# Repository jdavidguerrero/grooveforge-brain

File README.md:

# GrooveForge Brain

> *"Una pieza de hardware. Cinco niveles de superpoderes. Tú decidís hasta dónde llegar."*

Boutique hybrid AI synthesizer — Teensy 4.1 + ESP32-S3 + discrete 2N3904 ladder filter.

**Retail: $599 USD · BOM: ~$110 · Margin: 82%**

---

## The 5 Levels (North Star)

```
NIVEL 0 — STANDALONE   → 6 synth engines + analog ladder filter + 12 signature FX
NIVEL 1 — + MIDI KB    → Scale Lock, Chord Recognition, Beat Follower (TinyML)
NIVEL 2 — + SLAVES     → E-Drum, Marimba, Air-Bamboo ecosystem (v1.x)
NIVEL 3 — + WIFI       → Patch search NL, progression suggester (cloud AI)
NIVEL 4 — + DAW        → GroovePilot VST3 mix-aware co-pilot
```

---

## Architecture

| Component | Chip | Role |
|---|---|---|
| Audio Brain | Teensy 4.1 (Cortex-M7 @ 600MHz) | Synth engines, FX, TinyML, MIDI |
| Network + UI | ESP32-S3 + GC9A01 1.28" display | WiFi, BLE, cloud sync, OTA |
| Audio Codec | SGTL5000 | 24-bit/48kHz ADC + DAC |
| Analog Filter | Discrete 2N3904 ladder (Moog 1970) | THE analog character |

Audio path: `Teensy → I2S → SGTL5000 → 2N3904 ladder → SGTL5000 ADC → USB Audio`

---

## Monorepo Structure

```
apps/
├── firmware-teensy/   C++ — Teensy 4.1 (PlatformIO)
├── firmware-esp32/    C++ — ESP32-S3 (PlatformIO)
├── bridge-protocol/   C headers — shared protocol
├── hardware/          KiCad PCB schematics
├── design/            Industrial design (3D + Figma)
├── training/          Python — TinyML model training
└── docs/              OpenSpec documentation (SSoT)
tools/
├── matching-jig/      Arduino — transistor Vbe matching jig
└── filter-cal/        Calibration scripts
```

---

## Quick Start

```bash
# Build Teensy firmware
cd apps/firmware-teensy && pio run -e teensy41 -t upload

# Build ESP32 firmware
cd apps/firmware-esp32 && pio run -e esp32s3 -t upload

# Run tests (native, no hardware needed)
pnpm test:native

# ML training
cd apps/training && uv sync && uv run pytest
```

---

## Documentation

All specs live in [`apps/docs/`](apps/docs/README.md):

| Doc | Content |
|---|---|
| [00-master-strategy.md](apps/docs/00-master-strategy.md) | Vision, pricing, North Star |
| [01-architecture.md](apps/docs/01-architecture.md) | Hardware + software spec |
| [02-bridge-protocol.md](apps/docs/02-bridge-protocol.md) | Teensy ↔ ESP32 ↔ VST3 protocol |
| [03-filter-design.md](apps/docs/03-filter-design.md) | Discrete 2N3904 ladder filter |
| [04-ai-architecture.md](apps/docs/04-ai-architecture.md) | 3-layer AI spec |
| [05-fx-architecture.md](apps/docs/05-fx-architecture.md) | 12 signature effects |
| [06-implementation-roadmap.md](apps/docs/06-implementation-roadmap.md) | Phase & sprint plan |

---

## Status

**Phase 0 — Foundation** · May 2026 · 🟡 In Progress

| Milestone | Status |
|---|---|
| Monorepo + CLAUDE.md + agents + skills | 🟢 Done |
| Sprint 1.1 — Hello Tone (440Hz via I2S) | 🔴 Pending |
| Sprint 1.2 — Multi-OSC + ADSR | 🔴 Pending |
| Sprint 1.3 — Transistor matching jig | 🔴 Pending |
| Sprint 1.4 — Filter protoboard | 🔴 Pending |

---

*GrooveForge Brain · Juan Guerrero (GPROG) · Bogotá, Colombia · 2026*

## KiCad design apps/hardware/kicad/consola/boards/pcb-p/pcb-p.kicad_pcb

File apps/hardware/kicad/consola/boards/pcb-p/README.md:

# PCB-P — pads de fuerza Console

Placa pasiva de 223 × 31 × 1,6 mm, ensamblada a mano. Seis discos FSR402 sobre la placa;
colas por ranuras NPTH a seis sockets HCTL C2897365 inferiores. Se conservan seis JST-PH
J1–J6 de 2 vías y los doce nets independientes del mazo aprobado.

Especificación y cálculo: `docs/THEORY-layout.md`. Resultado y límites: `../../tools/layout/REPORT-p.md`.
Recrear layout con Python de KiCad: `../../tools/layout/layout_p.py`.
La terminación inferior reemplaza la soldadura directa D43.

`placement.csv`: coordenadas de panel, seis datums de disco F. `docs/layout-targets.json`: datums pin 1 de FSR/J B.
Conversión: x_panel=x_KiCad+44; y_panel=371−y_KiCad.
Gerbers y taladros en `fab/`; montaje 1:1 y comprobaciones en `docs/`.

Los identificadores FSR1–FSR6 del esquema se conservan para los landings de sus sockets inferiores.
La huella local reemplaza la geometría D43; su nombre histórico no indica soldadura directa.
La compra de sockets está en `assembly-sockets.csv`, validada con el mismo catálogo y comprobador BOM.

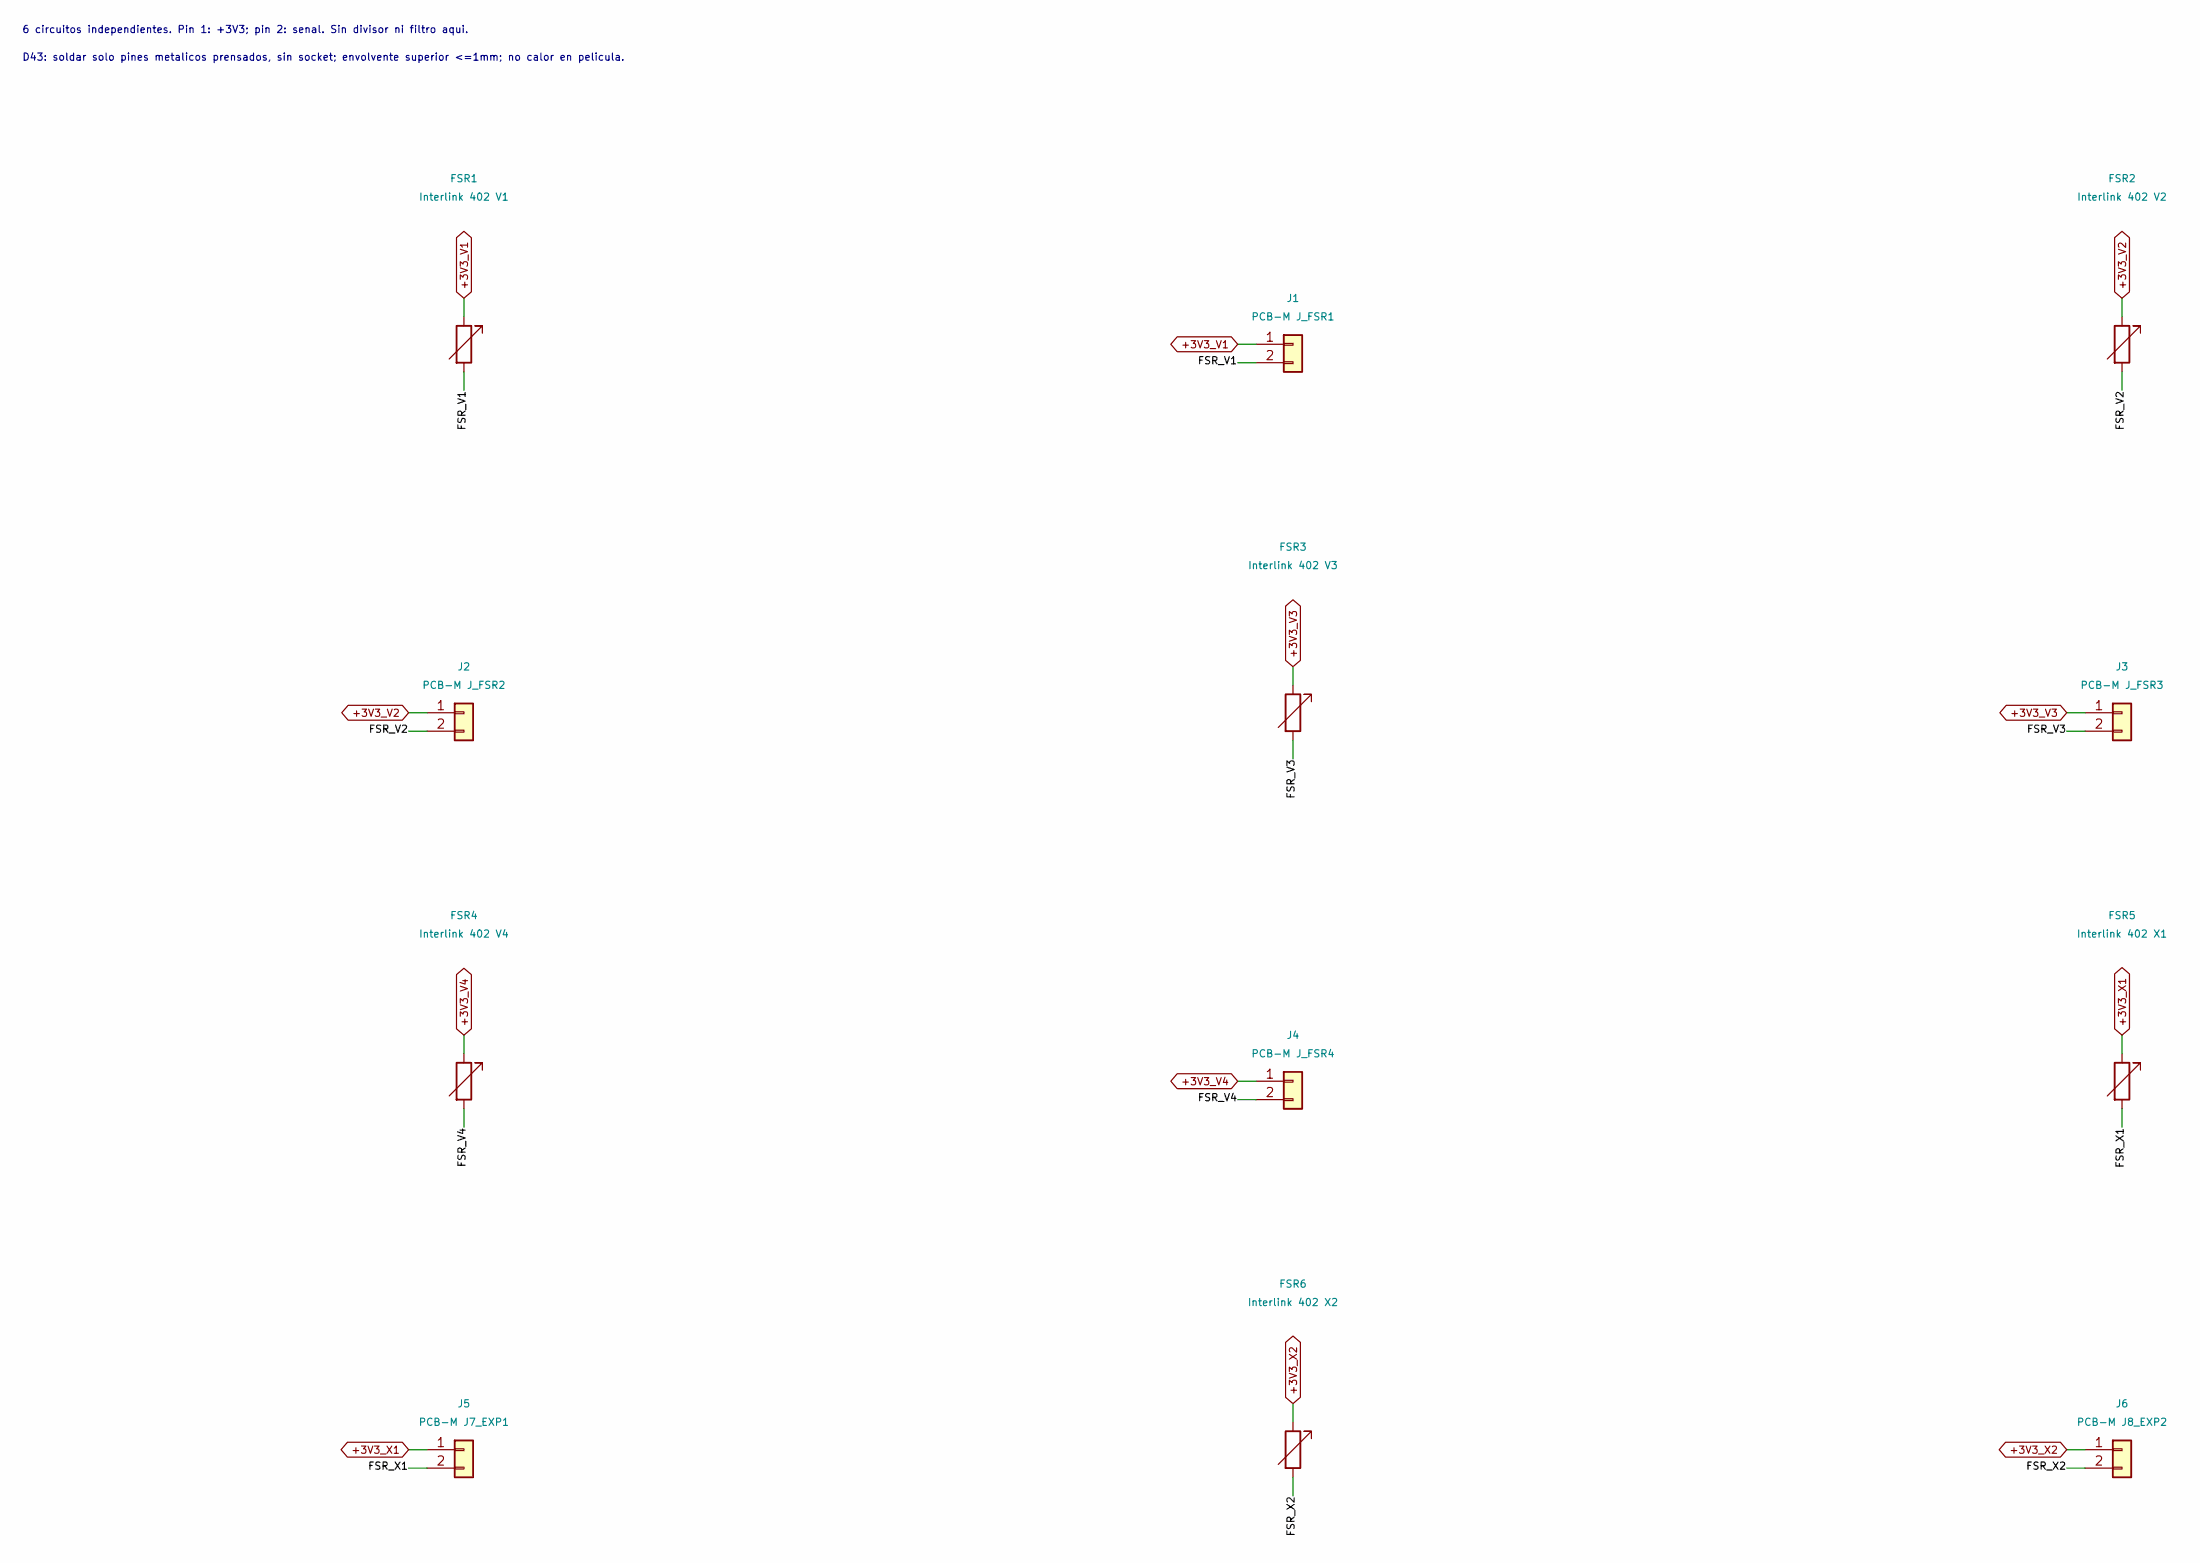
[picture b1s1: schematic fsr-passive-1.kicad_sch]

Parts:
FSR1: Interlink 402 V1; FSR402_DirectSolder_1x02_P2.54mm
FSR2: Interlink 402 V2; FSR402_DirectSolder_1x02_P2.54mm
FSR3: Interlink 402 V3; FSR402_DirectSolder_1x02_P2.54mm
FSR4: Interlink 402 V4; FSR402_DirectSolder_1x02_P2.54mm
FSR5: Interlink 402 X1; FSR402_DirectSolder_1x02_P2.54mm
FSR6: Interlink 402 X2; FSR402_DirectSolder_1x02_P2.54mm
J1: PCB-M J_FSR1; JST_PH_S2B-PH-K_1x02_P2.00mm_Horizontal; MPN S2B-PH-K-S(LF)(SN); LCSC C173752
J2: PCB-M J_FSR2; JST_PH_S2B-PH-K_1x02_P2.00mm_Horizontal; MPN S2B-PH-K-S(LF)(SN); LCSC C173752
J3: PCB-M J_FSR3; JST_PH_S2B-PH-K_1x02_P2.00mm_Horizontal; MPN S2B-PH-K-S(LF)(SN); LCSC C173752
J4: PCB-M J_FSR4; JST_PH_S2B-PH-K_1x02_P2.00mm_Horizontal; MPN S2B-PH-K-S(LF)(SN); LCSC C173752
J5: PCB-M J7_EXP1; JST_PH_S2B-PH-K_1x02_P2.00mm_Horizontal; MPN S2B-PH-K-S(LF)(SN); LCSC C173752
J6: PCB-M J8_EXP2; JST_PH_S2B-PH-K_1x02_P2.00mm_Horizontal; MPN S2B-PH-K-S(LF)(SN); LCSC C173752

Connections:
+3V3_V1: FSR1.1, J1.1
+3V3_V2: FSR2.1, J2.1
+3V3_V3: FSR3.1, J3.1
+3V3_V4: FSR4.1, J4.1
+3V3_X1: FSR5.1, J5.1
+3V3_X2: FSR6.1, J6.1
/fsr-passive-1/FSR_V1: FSR1.2, J1.2
/fsr-passive-1/FSR_V2: FSR2.2, J2.2
/fsr-passive-1/FSR_V3: FSR3.2, J3.2
/fsr-passive-1/FSR_V4: FSR4.2, J4.2
/fsr-passive-1/FSR_X1: FSR5.2, J5.2
/fsr-passive-1/FSR_X2: FSR6.2, J6.2

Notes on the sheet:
6 circuitos independientes. Pin 1: +3V3; pin 2: senal. Sin divisor ni filtro aqui.
D43: soldar solo pines metalicos prensados, sin socket; envolvente superior <=1mm; no calor en pelicula.

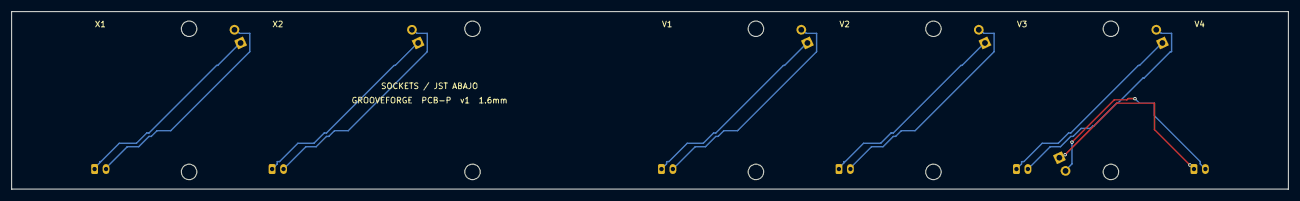
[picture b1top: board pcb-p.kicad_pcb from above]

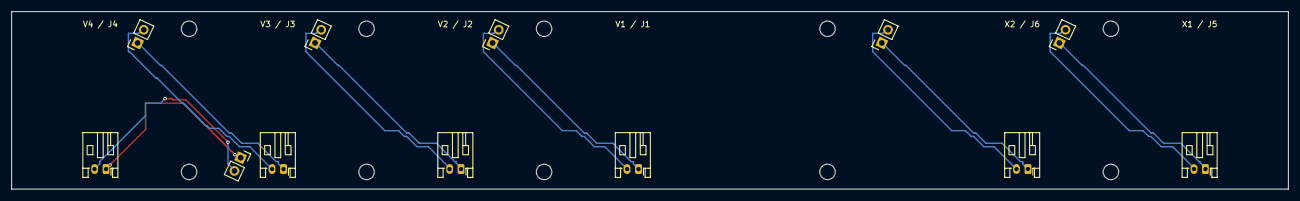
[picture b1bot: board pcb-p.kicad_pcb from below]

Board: 2 copper layers, 223.0 x 31.0 mm, 28 parts (12 on the bottom side), 12 nets.

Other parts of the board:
H1, H2, H3, H4, H5, H6, H7, H8, H9, H10: M2.5 NPTH; MountingHole_2.7mm_M2.5
SLOT1, SLOT2, SLOT3, SLOT4, SLOT5, SLOT6: COLA 3x8.8 NPTH

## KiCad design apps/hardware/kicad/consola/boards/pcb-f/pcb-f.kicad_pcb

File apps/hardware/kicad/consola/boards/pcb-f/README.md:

# PCB-F — GrooveForge Console

Layout de dos capas **81 × 83 mm**, cuatro RS6011 B50K a paso **20 mm**.
El esquema y los CSV originales se conservan. Ver [teoría](docs/THEORY-layout.md)
y [reporte completo](../../tools/layout/REPORT-f.md).

Desde la raíz del clon:

```sh
/Applications/KiCad/KiCad.app/Contents/Frameworks/Python.framework/Versions/Current/bin/python3 apps/hardware/kicad/consola/tools/layout/layout_f.py
```

El script exporta el esquema a XML, compara las seis redes con el XML verificado,
importa sus diez componentes, coloca cuatro M3, enruta, rellena GND, ejecuta DRC y
exporta `fab/` y `docs/`. `--verify-only` verifica la placa guardada;
`--finish-only` rellena, verifica y exporta una placa existente. No escribe esquemas.

Coordenadas: **x_panel = x_KiCad + 44; y_panel = 371 − y_KiCad** (mm).
Faders: F.Cu / 90°; centros según `placement.csv`. J1: **B.Cu / 90°**, origen
panel **(257,5; 160,2)**, boca hacia **−x**; su extremo trasero llega a y=165,1.
La posición deja libres el M3 posterior izquierdo y RV1. Cara superior del FR4:
TOP−9,5; con espesor 1,6, J1 se monta bajo TOP−11,1.

J1 es **1:1** hacia PCB-A J3: **1 +3V3, 2 FADER1, 3 FADER2, 4 FADER3,
5 FADER4, 6 GND**. Los MP del JST se conservan sin red, según el esquema.
Los doce MP de los faders llevan GND sólido. La copia local `groovepush.pretty`
conserva la geometría upstream y añade únicamente `zone_connect 2` a esos pads;
no cambia la biblioteca compartida ni el identificador del esquema.

`fab/`: Gerbers, taladros **PTH y NPTH separados**, job y reporte de taladros.
`docs/`: DRC JSON, verificación geométrica/eléctrica JSON, XML recién exportado,
SVG por capa, plantilla [1:1](docs/pcb-f-assembly-1to1.svg) y DXF Edge.Cuts.
Los agujeros internos se fabrican desde NPTH; el DXF de Edge.Cuts contiene solo
el perímetro exterior, sin convertir taladros en fresados duplicados.

**Antes de pedir:** imprimir el SVG de montaje al 100 %, sin ajustar a página;
medir el paso de 20 mm y el contorno, superponer un RS6011 real y verificar pads,
NPTH, carcasa, carrera, altura, cabezas M3 Ø5,5 y acceso al cable JST por debajo.
No usar arandelas Ø6,4 en las esquinas sin revisar el montaje. El contorno fijo deja
solo 0,25 mm entre cabeza nominal Ø5,5 y borde. Validar continuidad carcasa→GND
y el bond del panel: los cuatro agujeros M3 son NPTH y no realizan ese bond.

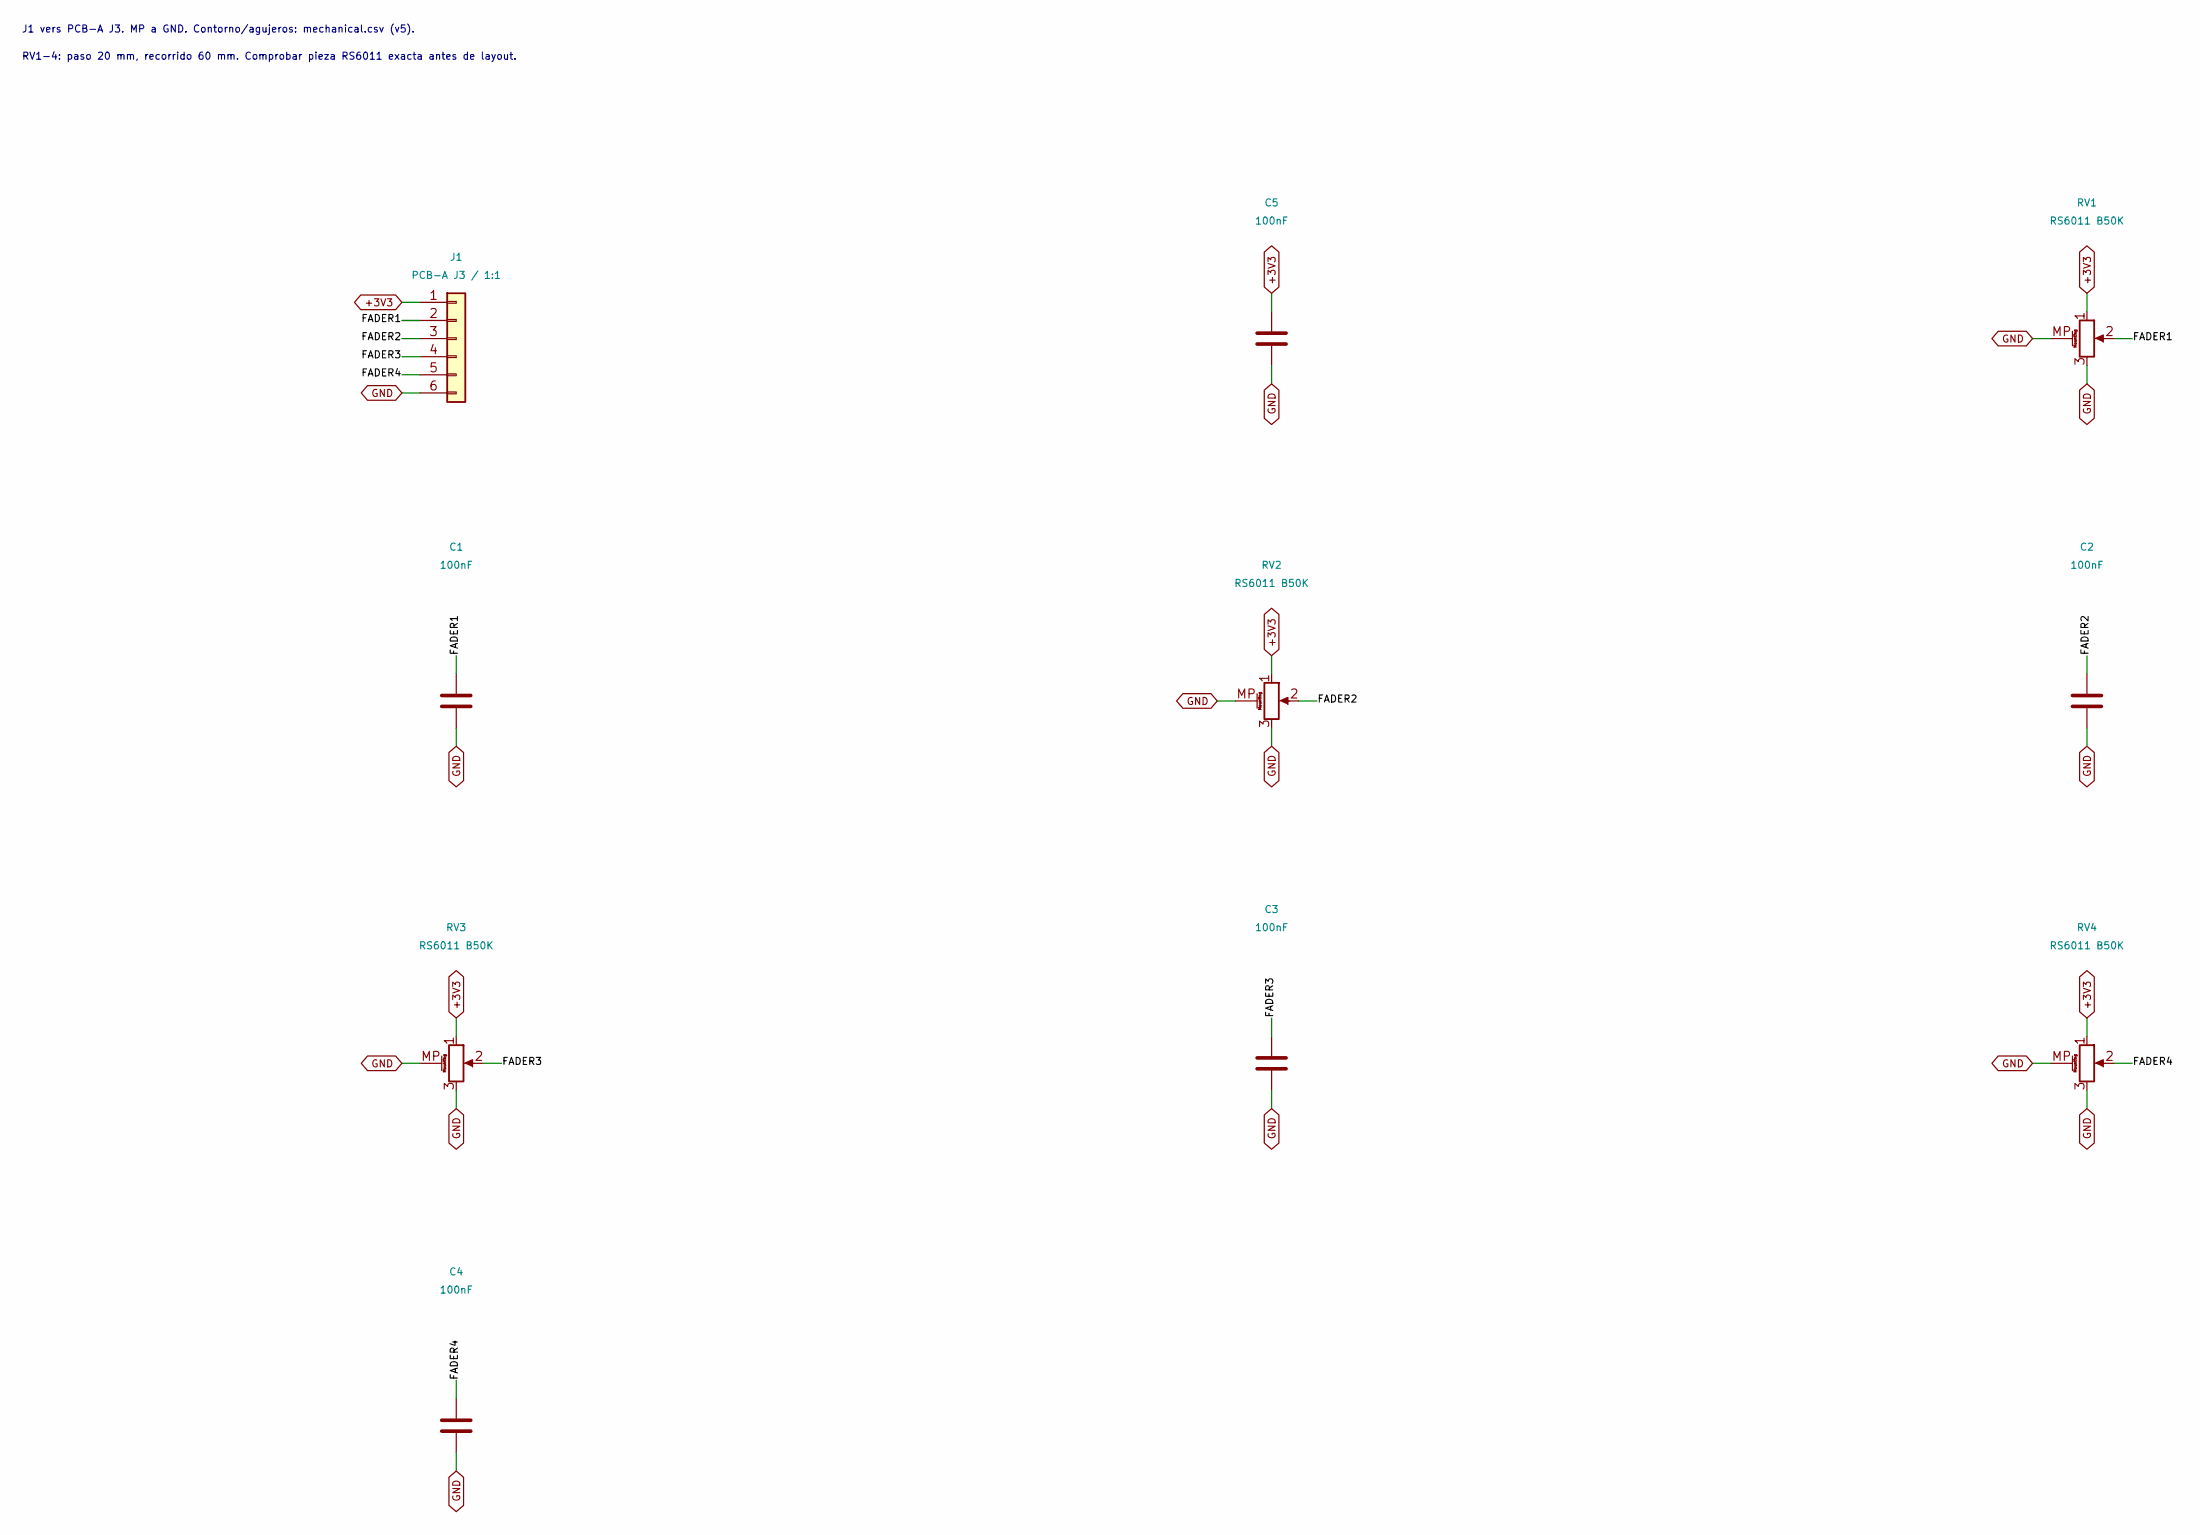
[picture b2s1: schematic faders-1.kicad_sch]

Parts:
C1, C2, C3, C4, C5: 100nF; C_0805_2012Metric; MPN CC0805KRX7R9BB104; LCSC C49678
J1: PCB-A J3 / 1:1; JST_SH_SM06B-SRSS-TB_1x06-1MP_P1.00mm_Horizontal; MPN SM06B-SRSS-TB(LF)(SN); LCSC C160405
RV1, RV2, RV3, RV4: RS6011 B50K; ALPS_RS6011P_60mm

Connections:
+3V3: C5.1, J1.1, RV1.1, RV2.1, RV3.1, RV4.1
/faders-1/FADER1: C1.1, J1.2, RV1.2
/faders-1/FADER2: C2.1, J1.3, RV2.2
/faders-1/FADER3: C3.1, J1.4, RV3.2
/faders-1/FADER4: C4.1, J1.5, RV4.2
GND: C1.2, C2.2, C3.2, C4.2, C5.2, J1.6, RV1.3, RV1.MP (MountPin), RV2.3, RV2.MP (MountPin), RV3.3, RV3.MP (MountPin), RV4.3, RV4.MP (MountPin)

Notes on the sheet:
J1 vers PCB-A J3. MP a GND. Contorno/agujeros: mechanical.csv (v5).
RV1-4: paso 20 mm, recorrido 60 mm. Comprobar pieza RS6011 exacta antes de layout.

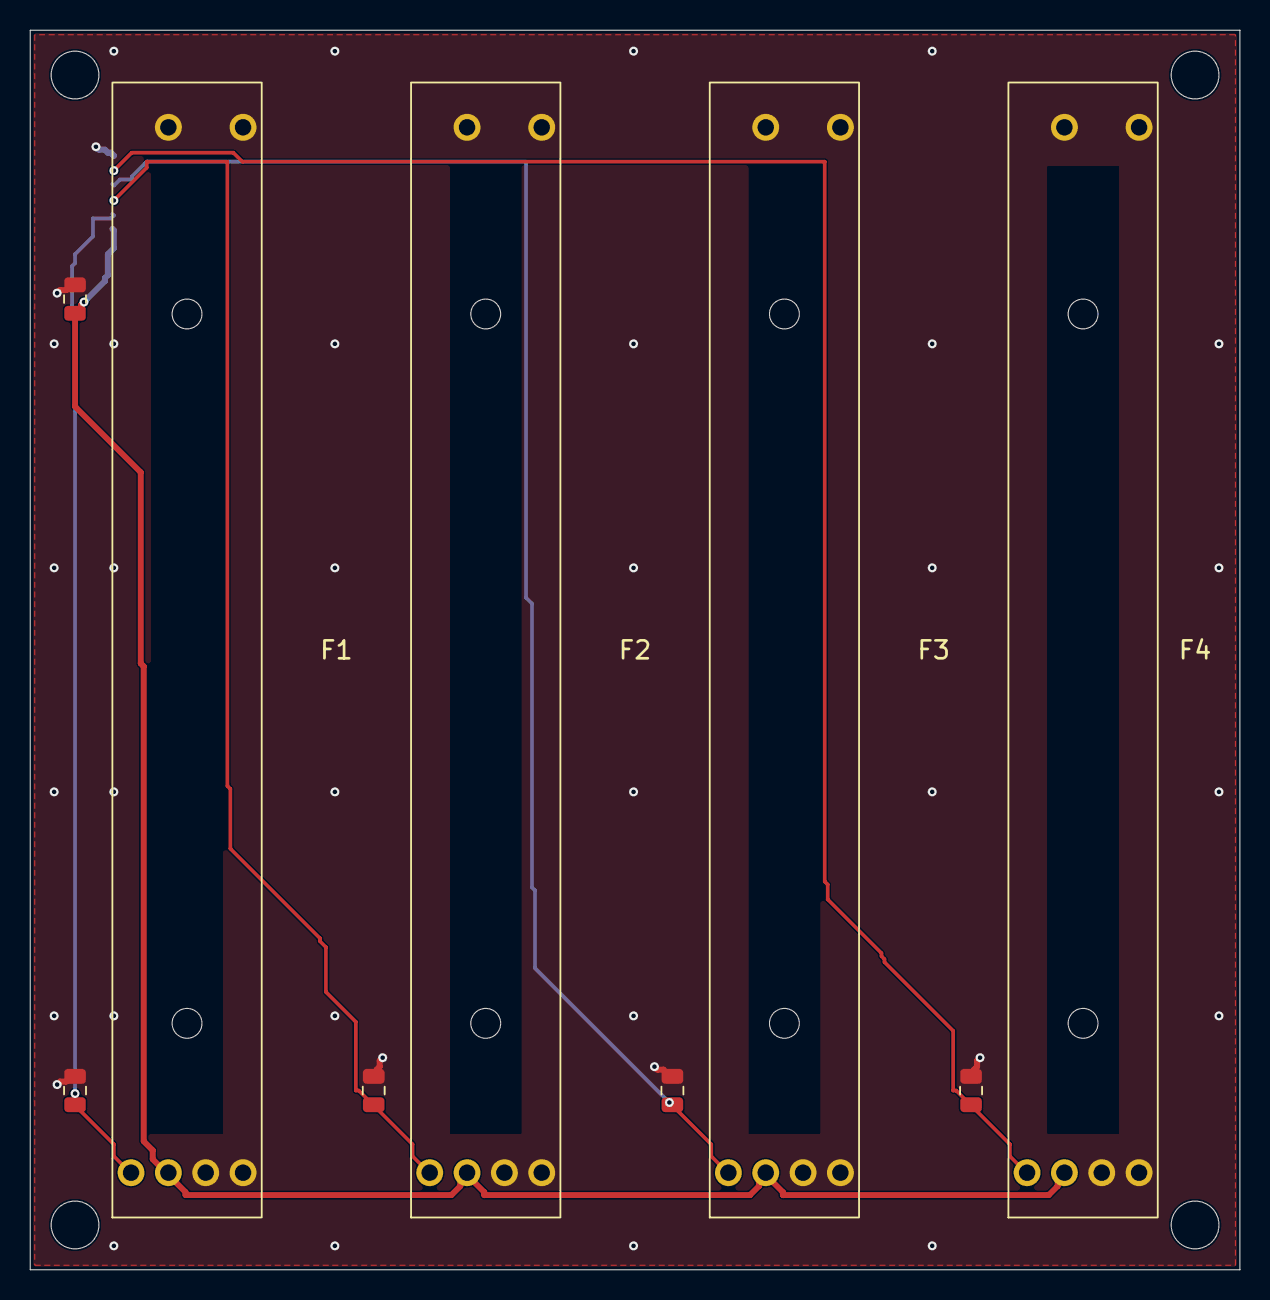
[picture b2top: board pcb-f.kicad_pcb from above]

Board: 2 copper layers, 81.0 x 83.0 mm, 14 parts (1 on the bottom side), 6 nets.

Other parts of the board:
H1, H2, H3, H4: M3; MountingHole_3.2mm_M3

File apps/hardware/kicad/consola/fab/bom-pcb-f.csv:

"Reference","Value","Footprint","LCSC","Supply","SupplyDescription","DNP"
"C1","100nF","Capacitor_SMD:C_0805_2012Metric","C49678","","",""
"C2","100nF","Capacitor_SMD:C_0805_2012Metric","C49678","","",""
"C3","100nF","Capacitor_SMD:C_0805_2012Metric","C49678","","",""
"C4","100nF","Capacitor_SMD:C_0805_2012Metric","C49678","","",""
"C5","100nF","Capacitor_SMD:C_0805_2012Metric","C49678","","",""
"J1","PCB-A J3 / 1:1","Connector_JST:JST_SH_SM06B-SRSS-TB_1x06-1MP_P1.00mm_Horizontal","C160405","","",""
"RV1","RS6011 B50K","groovepush:ALPS_RS6011P_60mm","","owner","Juan: cuatro faders RS6011 B50K",""
"RV2","RS6011 B50K","groovepush:ALPS_RS6011P_60mm","","owner","Juan: cuatro faders RS6011 B50K",""
"RV3","RS6011 B50K","groovepush:ALPS_RS6011P_60mm","","owner","Juan: cuatro faders RS6011 B50K",""
"RV4","RS6011 B50K","groovepush:ALPS_RS6011P_60mm","","owner","Juan: cuatro faders RS6011 B50K",""

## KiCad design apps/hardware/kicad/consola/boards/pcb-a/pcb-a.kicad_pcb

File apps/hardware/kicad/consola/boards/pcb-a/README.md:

# PCB-A — tira de encoders Console v1

Tira de dos capas, 217 × 29,6 mm, espesor 1,6 mm y esquinas R1. Esquema, referencias,
pads y redes conservados respecto a `edc67a3`. La validación de entrega está en
[REPORT-strip.md](REPORT-strip.md); el criterio previo está en [THEORY-strip.md](THEORY-strip.md).

## Montaje y coordenadas

Conversión: `x_panel = x_KiCad + 44`, `y_panel = 371 − y_KiCad` (mm).
Contorno KiCad: x=10…227, y=166,4…196. Contorno panel: x=54…271, y=175…204,6.
Ejes E1–E8 del CSV: x=79,105,131,157,183,209,235,261; y=192; paso 26 mm.
Los orígenes de las huellas EC11 están a (−7,5; −2,5) mm de sus ejes.

| Agujero | KiCad (mm) | Panel (mm) | Taladro |
|---|---|---|---|
| H1 | 40; 192 | 84; 179 | NPTH Ø3,2 mm |
| H2 | 74; 179 | 118; 192 | NPTH Ø3,2 mm |
| H3 | 100; 179 | 144; 192 | NPTH Ø3,2 mm |
| H4 | 204; 179 | 248; 192 | NPTH Ø3,2 mm |

H4 está entre E7 y E8 para liberar el cuerpo del último encoder. Las posiciones también
están anotadas en `Cmts.User` de la PCB. H1 se llevó a (84;179) panel: libera TAP, la franja de navegación de PCB-K izquierda (x 68–74,5) y los recortes de la chapa.
Separadores BSO-M3 de **18 mm útiles**: cara inferior de chapa z83 → PCB-A superior z65 (TOP−20, doc25 §7).
La chapa lleva cuatro cortes Ø4,2, alimentados por el CSV v5 y `PEM_HOLE`.
Puentes láser mínimos: **4,2 / 7,35 / 7,35 / 7,35 mm**. El cuerpo Ø5,6 de los separadores
no invade K combinado ni las particiones izq./der.; H1 deja 1,2 mm al borde.
Ver [chequeo de montaje](../../tools/fit/REPORT-pcba-mounting.md) y
[BOM de herrajes](../../../../../design/3d-models/consola/BOM-herrajes.md). Los NPTH no constituyen una unión eléctrica a la chapa.

J1 es IDC 2×15 por la cara inferior, con su eje largo paralelo a X; origen KiCad
(207,78;192,07), ángulo +90°. J2 SH4 y J3 SH6 van en la cara inferior; J3 abre hacia
la derecha. U1 y los pasivos quedan dentro de la tira. **R1, R2 y J4 son DNP**;
los pull-ups activos de I2C están en PCB-M. Los pads DNP conservan sus pistas y redes.
Pinout y cables 1:1: [CONNECTORS.md](../CONNECTORS.md).

`Connector_IDC.pretty/` conserva los pads, taladros, cuerpo y courtyard de la huella IDC.
Solo adapta la marca de pin 1 de serigrafía al borde de la tira; la tabla local resuelve
el mismo identificador de huella sin modificar el esquema. El triángulo original se
conserva en `Dwgs.User`, y el marcador de fabricación permanece en `B.Fab`.

## Cobre y archivos de fabricación

Señales 0,25 mm; +3V3, +5V y pistas GND ≥0,4 mm; separación ≥0,2 mm;
vías Ø0,6/taladro Ø0,3 mm. Hay planos GND en ambas caras y costura. Los MP de
los ocho encoders se conectan a GND de forma sólida. Las reglas del proyecto y
`pcb-a.kicad_dru` verifican los mínimos; no se excluyen errores de cobre.

- `fab/`: Gerber, taladros PTH/NPTH y ZIP para fabricación.
- `docs/`: SVG de capas, informe DRC final y verificación de integridad.
- `../../tools/fit/REPORT-pcba-fit.md`: encaje geométrico y corredores del mazo.

No usar capturas o DRC de colocación como aprobación de fabricación. La continuidad
chapa/eje→GND, alturas reales, radios de los cables, tolerancias y accesibilidad de
separadores requieren montaje físico. El diagnóstico de PCB-K usa contornos históricos
y se detalla como limitación del informe de encaje.

## Reproducir validaciones

Desde la raíz del clon, con KiCad 10.0.6 instalado:

```sh
KPY=/Applications/KiCad/KiCad.app/Contents/Frameworks/Python.framework/Versions/Current/bin/python3
KCLI=/Applications/KiCad/KiCad.app/Contents/MacOS/kicad-cli
BOARD=apps/hardware/kicad/consola/boards/pcb-a
"$KPY" -B tools/layout/pcba_strip.py verify
"$KCLI" pcb drc --schematic-parity --format json --exit-code-violations -o "$BOARD/docs/drc-final.json" "$BOARD/pcb-a.kicad_pcb"
python3 -B apps/hardware/kicad/consola/tools/fit/check_pcba_fit.py
python3 -B apps/hardware/kicad/consola/tools/fit/check_pcba_mounting.py
"$KPY" -B tools/layout/pcba_strip.py export
```

El script `tools/layout/pcba_strip.py` también contiene los pasos de colocación,
ruteo y relleno. El ruteo usa Freerouting y completa ramas pendientes con la grilla
del repositorio; cada resultado debe pasar de nuevo por DRC. `audit_copper` es un
diagnóstico SWIG sin comprobación de biblioteca; **no sustituye** el DRC CLI final.

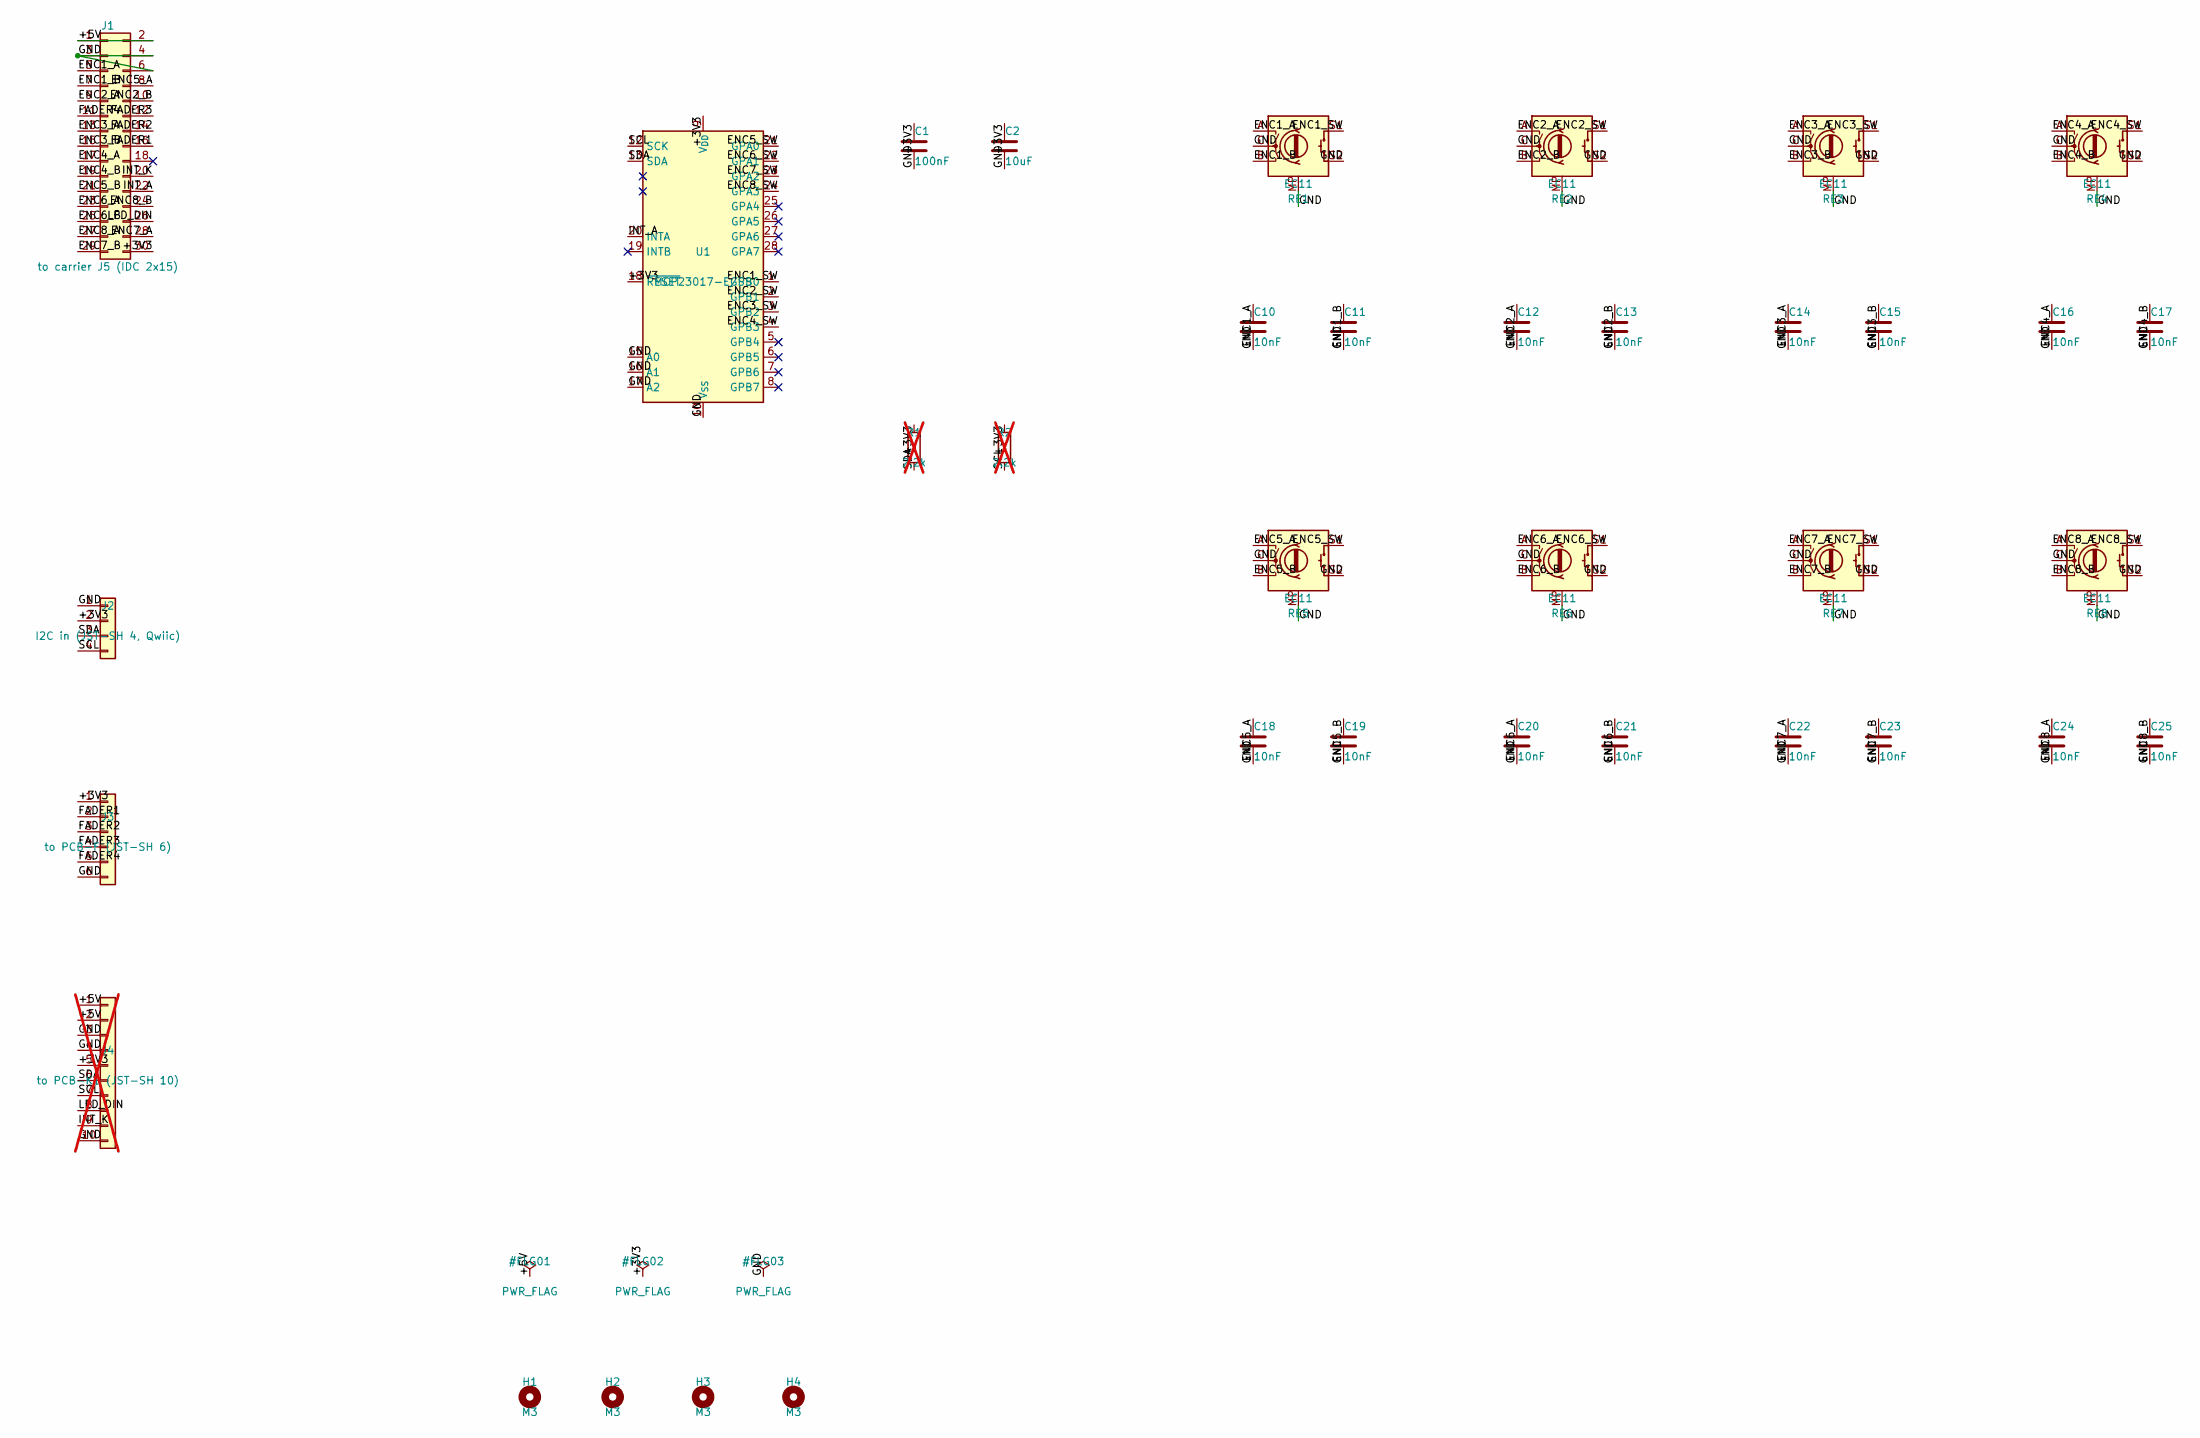
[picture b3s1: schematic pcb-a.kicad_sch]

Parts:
C1: 100nF; C_0603_1608Metric; LCSC C14663
C2: 10uF; C_0805_2012Metric; LCSC C15850
C10, C11, C12, C13, C14, C15, C16, C17, C18, C19, C20, C21, C22, C23, C24, C25: 10nF; C_0603_1608Metric; LCSC C57112
H1, H2, H3, H4: M3; MountingHole_3.2mm_M3
J1: to carrier J5 (IDC 2x15); IDC-Header_2x15_P2.54mm_Vertical
J2: I2C in (JST-SH 4, Qwiic); JST_SH_SM04B-SRSS-TB_1x04-1MP_P1.00mm_Horizontal; LCSC C160404
J3: to PCB-F (JST-SH 6); JST_SH_SM06B-SRSS-TB_1x06-1MP_P1.00mm_Horizontal; LCSC C160405
J4: to PCB-K1 (JST-SH 10); JST_SH_SM10B-SRSS-TB_1x10-1MP_P1.00mm_Horizontal; LCSC C160409; not fitted
R1, R2: 2.2k; R_0603_1608Metric; LCSC C4190; not fitted
RE1, RE2, RE3, RE4, RE5, RE6, RE7, RE8: EC11; RotaryEncoder_Alps_EC11E-Switch_Vertical_H20mm
U1: MCP23017-E/SS; SSOP-28_5.3x10.2mm_P0.65mm; LCSC C506653

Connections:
/+3V3: C1.1, C2.1, J1.30, J2.2, J3.1, J4.5, R1.1, R2.1, U1.9 (V_{DD}), U1.18 (~RESET)
/+5V: J1.1, J1.2, J4.1, J4.2
/ENC1_A: C10.1, J1.5, RE1.A
/ENC1_B: C11.1, J1.7, RE1.B
/ENC1_SW: RE1.S1, U1.1 (GPB0)
/ENC2_A: C12.1, J1.9, RE2.A
/ENC2_B: C13.1, J1.10, RE2.B
/ENC2_SW: RE2.S1, U1.2 (GPB1)
/ENC3_A: C14.1, J1.13, RE3.A
/ENC3_B: C15.1, J1.15, RE3.B
/ENC3_SW: RE3.S1, U1.3 (GPB2)
/ENC4_A: C16.1, J1.17, RE4.A
/ENC4_B: C17.1, J1.19, RE4.B
/ENC4_SW: RE4.S1, U1.4 (GPB3)
/ENC5_A: C18.1, J1.8, RE5.A
/ENC5_B: C19.1, J1.21, RE5.B
/ENC5_SW: RE5.S1, U1.21 (GPA0)
/ENC6_A: C20.1, J1.23, RE6.A
/ENC6_B: C21.1, J1.25, RE6.B
/ENC6_SW: RE6.S1, U1.22 (GPA1)
/ENC7_A: C22.1, J1.28, RE7.A
/ENC7_B: C23.1, J1.29, RE7.B
/ENC7_SW: RE7.S1, U1.23 (GPA2)
/ENC8_A: C24.1, J1.27, RE8.A
/ENC8_B: C25.1, J1.24, RE8.B
/ENC8_SW: RE8.S1, U1.24 (GPA3)
/FADER1: J1.16, J3.2
/FADER2: J1.14, J3.3
/FADER3: J1.12, J3.4
/FADER4: J1.11, J3.5
/GND: C1.2, C2.2, C10.2, C11.2, C12.2, C13.2, C14.2, C15.2, C16.2, C17.2, C18.2, C19.2, C20.2, C21.2, C22.2, C23.2, C24.2, C25.2, J1.3, J1.4, J1.6, J2.1, J3.6, J4.3, J4.4, J4.10, RE1.C, RE1.MP, RE1.S2, RE2.C, RE2.MP, RE2.S2, RE3.C, RE3.MP, RE3.S2, RE4.C, RE4.MP, RE4.S2, RE5.C, RE5.MP, RE5.S2, RE6.C, RE6.MP, RE6.S2, RE7.C, RE7.MP, RE7.S2, RE8.C, RE8.MP, RE8.S2, U1.10 (V_{SS}), U1.15 (A0), U1.16 (A1), U1.17 (A2)
/INT_A: J1.22, U1.20 (INTA)
/INT_K: J1.20, J4.9
/LED_DIN: J1.26, J4.8
/SCL: J2.4, J4.7, R2.2, U1.12 (SCK)
/SDA: J2.3, J4.6, R1.2, U1.13 (SDA)

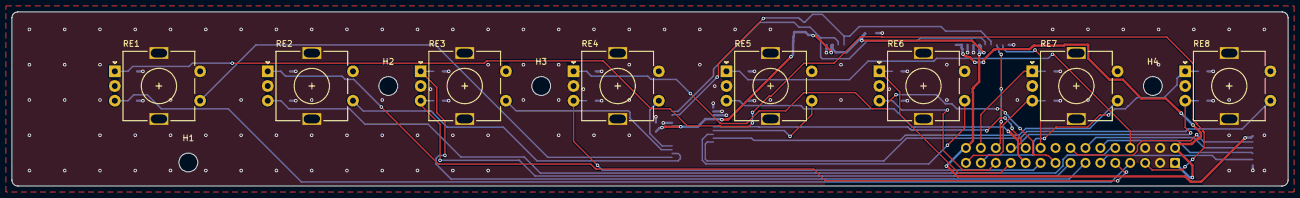
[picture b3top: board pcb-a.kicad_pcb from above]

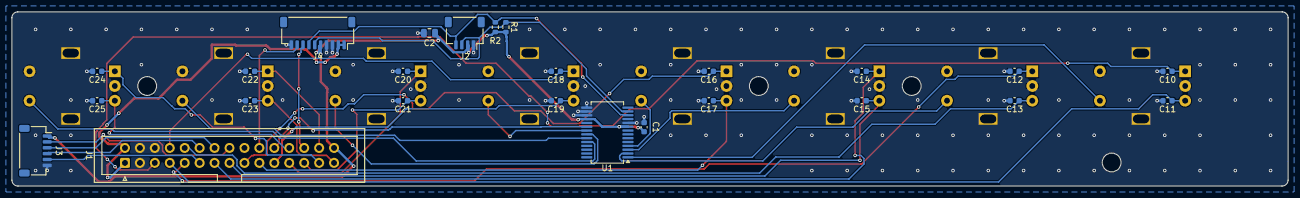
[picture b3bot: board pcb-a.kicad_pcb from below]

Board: 2 copper layers, 217.0 x 29.6 mm, 37 parts (25 on the bottom side), 36 nets.

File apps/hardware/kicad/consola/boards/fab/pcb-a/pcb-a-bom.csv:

Comment,Designator,Footprint,LCSC Part #
100nF,C1,C_0603_1608Metric,C14663
10uF,C2,C_0805_2012Metric,C15850
10nF,"C10,C11,C12,C13,C14,C15,C16,C17,C18,C19,C20,C21,C22,C23,C24,C25",C_0603_1608Metric,C57112
SM04B-SRSS-TB,J2,JST_SH_SM04B-SRSS-TB_1x04-1MP_P1.00mm_Horizontal,C160404
SM06B-SRSS-TB,J3,JST_SH_SM06B-SRSS-TB_1x06-1MP_P1.00mm_Horizontal,C160405
SM10B-SRSS-TB,J4,JST_SH_SM10B-SRSS-TB_1x10-1MP_P1.00mm_Horizontal,C160409
2.2k,"R1,R2",R_0603_1608Metric,C4190
MCP23017T-E/SS,U1,SSOP-28_5.3x10.2mm_P0.65mm,C558584
